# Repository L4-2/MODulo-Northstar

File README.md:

##

## Authors

- [@L42](https://www.github.com/L4-2)

## License

# Northstar

This is the MODulo mouse development board. The Kicad project files are for Kicad 9.0 and above. You are free to use this design for your own use (non-commercial) as long as you credit here in some way.

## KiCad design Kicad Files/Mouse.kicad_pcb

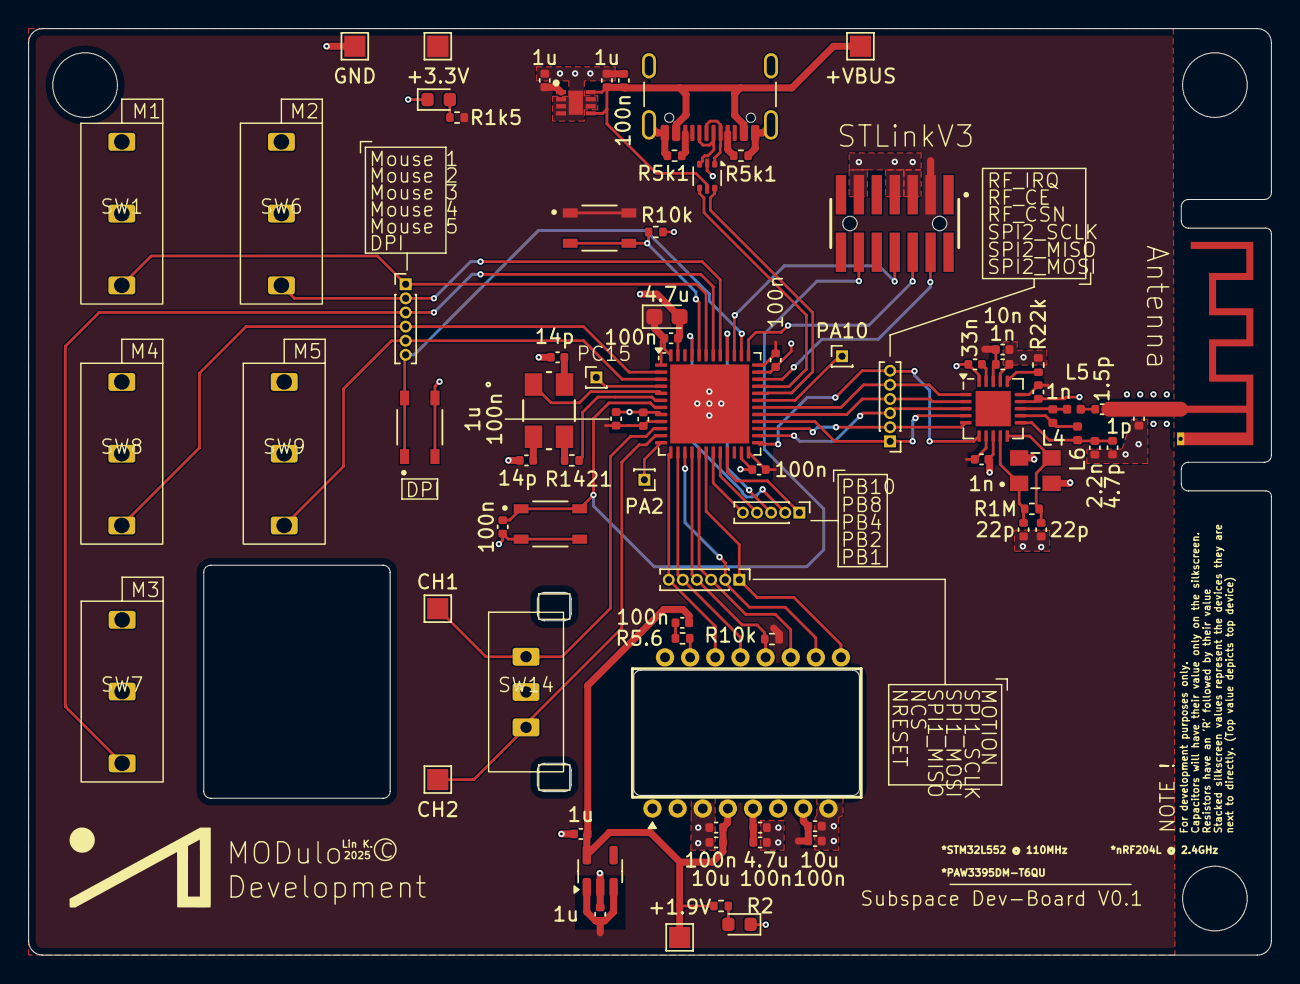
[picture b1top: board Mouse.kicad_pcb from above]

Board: 2 copper layers, 88.0 x 65.6 mm, 80 parts (0 on the bottom side), 62 nets.

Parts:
1.5p: 1.5p; C_0402_1005Metric
1n, 1n#2, 1n#3: 1n; C_0402_1005Metric
1p: 1p; C_0402_1005Metric
1u, 1u#2, 1u#3, 1u#4, 1u#5: 1u; C_0402_1005Metric
2.2n: 2.2n; C_0402_1005Metric
4.7p: 4.7p; C_0402_1005Metric
4.7u: 4.7u; C_0402_1005Metric
4.7u#2: 4.7u; CP_EIA-2012-12_Kemet-R
10n: 10n; C_0402_1005Metric
10u, 10u#2: 10u; C_0402_1005Metric
14p, 14p#2: 14p; C_0402_1005Metric
22p, 22p#2: 22p; C_0402_1005Metric
33n: 33n; C_0402_1005Metric
100n, 100n#2, 100n#3, 100n#4, 100n#5, 100n#6, 100n#7, 100n#8, 100n#9, 100n#10: 100n; C_0402_1005Metric
 +3.3V : TestPoint; TestPoint_Pad_1.5x1.5mm
+1.9V: TestPoint; TestPoint_Pad_1.5x1.5mm
+VBUS: TestPoint; TestPoint_Pad_1.5x1.5mm
AE2: Antenna; Texas_SWRA117D_2.4GHz_Left
CH1, CH2: TestPoint; TestPoint_Pad_1.5x1.5mm
D1, D2: LED; LED_0603_1608Metric
GND: TestPoint; TestPoint_Pad_1.5x1.5mm
IC1: TPS7A2133PQWDSGRQ1; SON50P200X200X80-9N
J1, J2, J9: Conn_01x06_Pin; PinHeader_1x06_P1.00mm_Vertical
J3: Conn_01x05_Pin; PinHeader_1x05_P1.00mm_Vertical
J4: USB4105-GF-A; USB_C_Receptacle_GCT_USB4105-xx-A_16P_TopMnt_Horizontal
J8: Conn_01x01_Pin; PinHeader_1x01_P1.00mm_Vertical
J12: FTSH-107-01-L-DV-K-A; SAMTEC_FTSH-107-01-L-DV-K-A
L4: 8.2n; L_0402_1005Metric
L5: 3.9n; L_0402_1005Metric
L6: 2.7n; L_0402_1005Metric
PA2, PA10: Conn_01x01_Pin; PinHeader_1x01_P1.00mm_Vertical
R1M: 1M; R_0402_1005Metric
R1k5, R2: 1k5; R_0402_1005Metric
R5.6: 5.6; R_0402_1005Metric
R5k1, R5k1#2: 5k1; R_0402_1005Metric
R10k, R10k#2: 10k; R_0402_1005Metric
R22k: 22k; R_0402_1005Metric
R1421: 1421; R_0402_1005Metric
S1, S2, S3: SKRPABE010; SW_SKRPABE010
SW1, SW6, SW7, SW8, SW9: SW_Push_SPDT; Huano
SW14: RotaryEncoder
U8: USBLC6-2P6; SOT-666
U10: nRF24L01P; QFN-20-1EP_4x4mm_P0.5mm_EP2.5x2.5mm
U11: TLV70019_SOT23-5; SOT-23-5
U12: PMW3360DM-T2QU; PMW3360
U14: STM32L552CEUxP; QFN-48-1EP_7x7mm_P0.5mm_EP5.6x5.6mm
XTAL2: ECS-80-12-30BQ-JES-TR; ECS-80-12_ECS
Y1: ECS-160-12-33Q-JES-TR; XTAL_ECS-160-12-33Q-JES-TR

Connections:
+1.9V: 1u#4.1, 10u#2.1, 100n#4.1, 100n#5.1, +1.9V.1, R2.2, U11.5 (OUT), U12.4 (VDD)
+3.3V: 1n.1, 1n#2.1, 1n#3.1, 1u#2.1, 1u#3.1, 1u#5.1, 4.7u#2.1, 10n.1, 10u.1, 100n#2.1, 100n#6.1, 100n#7.1, 100n#8.1, 100n#10.1, +3.3V.1, IC1.1 (OUT_1), J12.03, R1k5.2, R10k#2.1, S3.1, S3.2, U10.7 (VDD), U10.15 (VDD), U10.18 (VDD), U11.1 (IN), U11.3 (EN), U12.7 (VDDIO), U14.1 (VBAT), U14.9 (VDDA), U14.24 (VDD), U14.36 (VDD), U14.48 (VDD)
/BOOT: R10k.2, S3.3, S3.4, U14.44 (PH3)
/DPI: J9.6, S1.1, S1.2, U14.38 (PA15)
/Mouse1: J9.1, SW1.3 (C), U14.43 (PB7)
/Mouse2: J9.2, SW6.3 (C), U14.41 (PB5)
/Mouse3: J9.3, SW7.3 (C), U14.42 (PB6)
/Mouse4: J9.4, SW8.3 (C), U14.2 (PC13)
/Mouse5: J9.5, SW9.3 (C), U14.3 (PC14)
/NRESET: 100n#9.2, J12.12, S2.1, S2.2, U14.7 (NRST)
/RF_CE: J2.5, U10.1 (CE), U14.30 (PA9)
/RF_CSN: J2.4, U10.2 (CSN), U14.29 (PA8)
/RF_IRQ: J2.6, U10.6 (IRQ), U14.25 (PB12)
/SENSOR_MOTION: J1.1, U12.9 (MOTION), U14.18 (PB0)
/SENSOR_NCS: J1.5, U12.13 (NCS), U14.14 (PA4)
/SENSOR_NRESET: J1.6, U12.14 (NRESET), U14.13 (PA3)
/SPI1_MISO: J1.4, R10k#2.2, U12.12 (MISO), U14.16 (PA6)
/SPI1_MOSI: J1.3, U12.11 (MOSI), U14.17 (PA7)
/SPI1_SCLK: J1.2, U12.10 (SCLK), U14.15 (PA5)
/SPI2_MISO: J2.2, U10.5 (MISO), U14.27 (PB14)
/SPI2_MOSI: J2.1, U10.4 (MOSI), U14.28 (PB15)
/SPI2_SCLK: J2.3, U10.3 (SCK), U14.26 (PB13)
/SWCLK: J12.06, U14.37 (PA14)
/SWDIO: J12.04, U14.34 (PA13)
/SWO: J12.08, U14.39 (PB3)
/TIM2_CH1: CH1.1, SW14.A, U14.10 (PA0)
/TIM2_CH2: CH2.1, SW14.B, U14.11 (PA1)
/USB_DN: U8.6 (I/O1), U14.32 (PA11)
/USB_DP: U8.4 (I/O2), U14.33 (PA12)
GND: 1n.2, 1n#2.2, 1n#3.2, 1p.2, 1u.2, 1u#2.2, 1u#3.2, 1u#4.2, 1u#5.2, 2.2n.2, 4.7p.2, 4.7u.2, 4.7u#2.2, 10n.2, 10u.2, 10u#2.2, 14p.2, 14p#2.2, 22p.2, 22p#2.2, 33n.2, 100n.2, 100n#2.2, 100n#3.2, 100n#5.2, 100n#6.2, 100n#7.2, 100n#8.2, 100n#9.1, 100n#10.2, D1.1 (K), D2.1 (K), GND.1, IC1.2 (OUT_2), IC1.3 (NC_1), IC1.4 (GND), IC1.6 (NC_2), IC1.7 (IN_1), IC1.9 (EP), J4.A1 (GND), J4.A12 (GND), J4.B1 (GND), J4.B12 (GND), J4.S1 (SHIELD), J12.05, J12.07, J12.11, R5k1.1, R5k1#2.1, R10k.1, R22k.2, S1.3, S1.4, S2.3, S2.4, SW1.2 (B), SW6.2 (B), SW7.2 (B), SW8.2 (B), SW9.2 (B), SW14.C, U8.2 (GND), U10.8 (VSS), U10.14 (VSS), U10.17 (VSS), U10.20 (VSS), U11.2 (GND), U12.3 (GND), U12.8 (GNDIO), U14.8 (VSSA), U14.23 (VSS), U14.35 (VSS), U14.47 (VSS), U14.49 (VSS), Y1.2 (GND), Y1.4 (GND__1)
unnamed: 1.5p.2, 1p.1, AE2.1 (A)
unnamed: 1.5p.1, L5.2
unnamed: 100n#4.2, R5.6.2
unnamed: 14p#2.1, XTAL2.4
unnamed: 14p.1, XTAL2.2
unnamed: D1.2 (A), R1k5.1
unnamed: D2.2 (A), R2.1
unnamed: J3.1, U14.21 (PB10)
unnamed: J3.2, U14.45 (PB8)
unnamed: J3.3, U14.40 (PB4)
unnamed: J3.4, U14.20 (PB2)
unnamed: J3.5, U14.19 (PB1)
unnamed: J4.A5 (CC1), R5k1.2
unnamed: J4.B5 (CC2), R5k1#2.2
unnamed: J4.A6 (D+), J4.B6 (D+), U8.3 (I/O2)
unnamed: J4.A7 (D-), J4.B7 (D-), U8.1 (I/O1)
unnamed: J8.1, U14.4 (PC15)
unnamed: PA10.1, U14.31 (PA10)
unnamed: PA2.1, U14.12 (PA2)
unnamed: R1421.2, XTAL2.3
unnamed: L4.2, L6.1, U10.12 (ANT1)
unnamed: L4.1, L5.1, U10.13 (ANT2)
unnamed: 33n.1, U10.19 (DVDD)
unnamed: R22k.1, U10.16 (IREF)
unnamed: 2.2n.1, 4.7p.1, L6.2, U10.11 (VDD_PA)
unnamed: 22p.1, R1M.2, U10.10 (XC1), Y1.3 (OUT/IN)
unnamed: 22p#2.1, R1M.1, U10.9 (XC2), Y1.1 (IN/OUT)
unnamed: R5.6.1, U12.15 (LED_P)
unnamed: 4.7u.1, 100n#3.1, U12.5 (VDDREG)
unnamed: U14.5 (PH0), XTAL2.1
unnamed: R1421.1, U14.6 (PH1)
VBUS: 1u.1, 100n.1, +VBUS.1, IC1.5 (EN), IC1.8 (IN_2), J4.A4 (VBUS), J4.A9 (VBUS), J4.B4 (VBUS), J4.B9 (VBUS), U8.5 (VBUS)

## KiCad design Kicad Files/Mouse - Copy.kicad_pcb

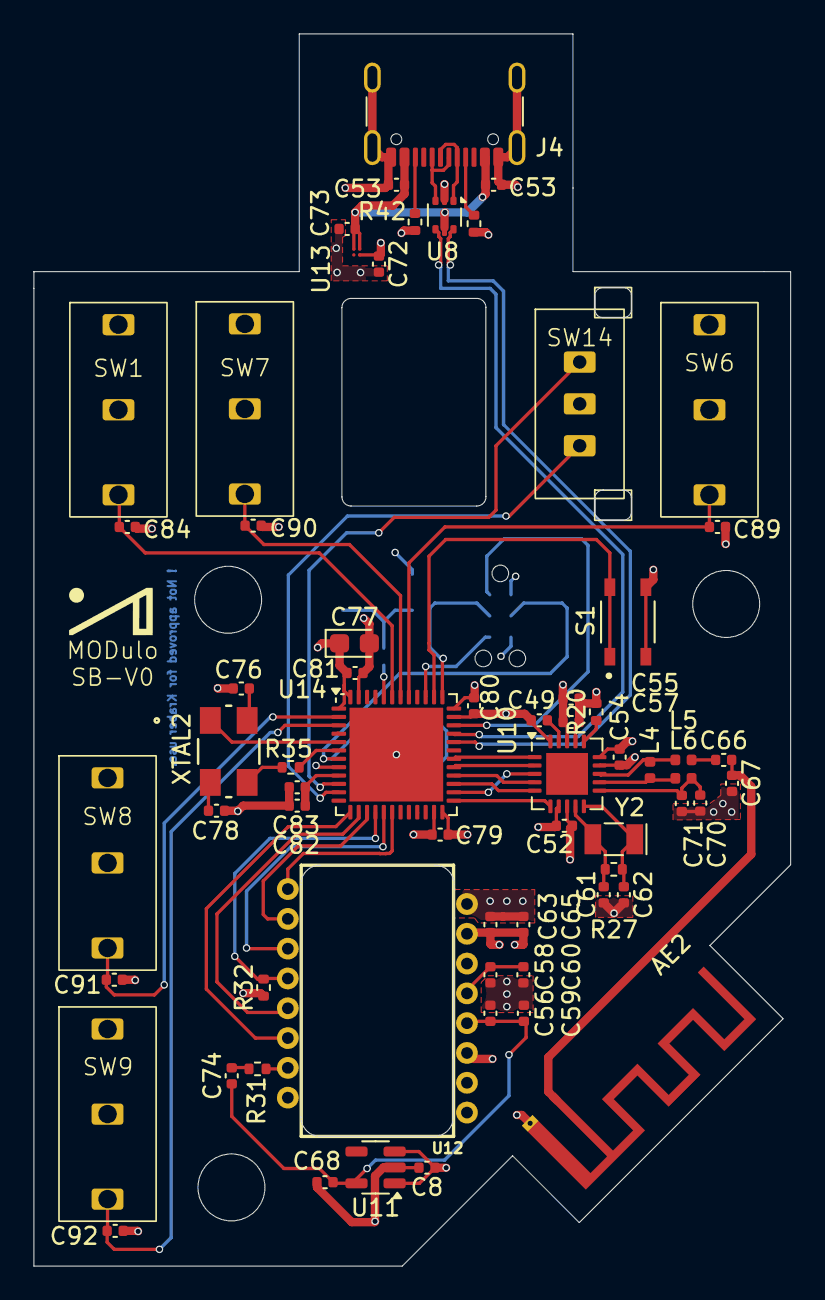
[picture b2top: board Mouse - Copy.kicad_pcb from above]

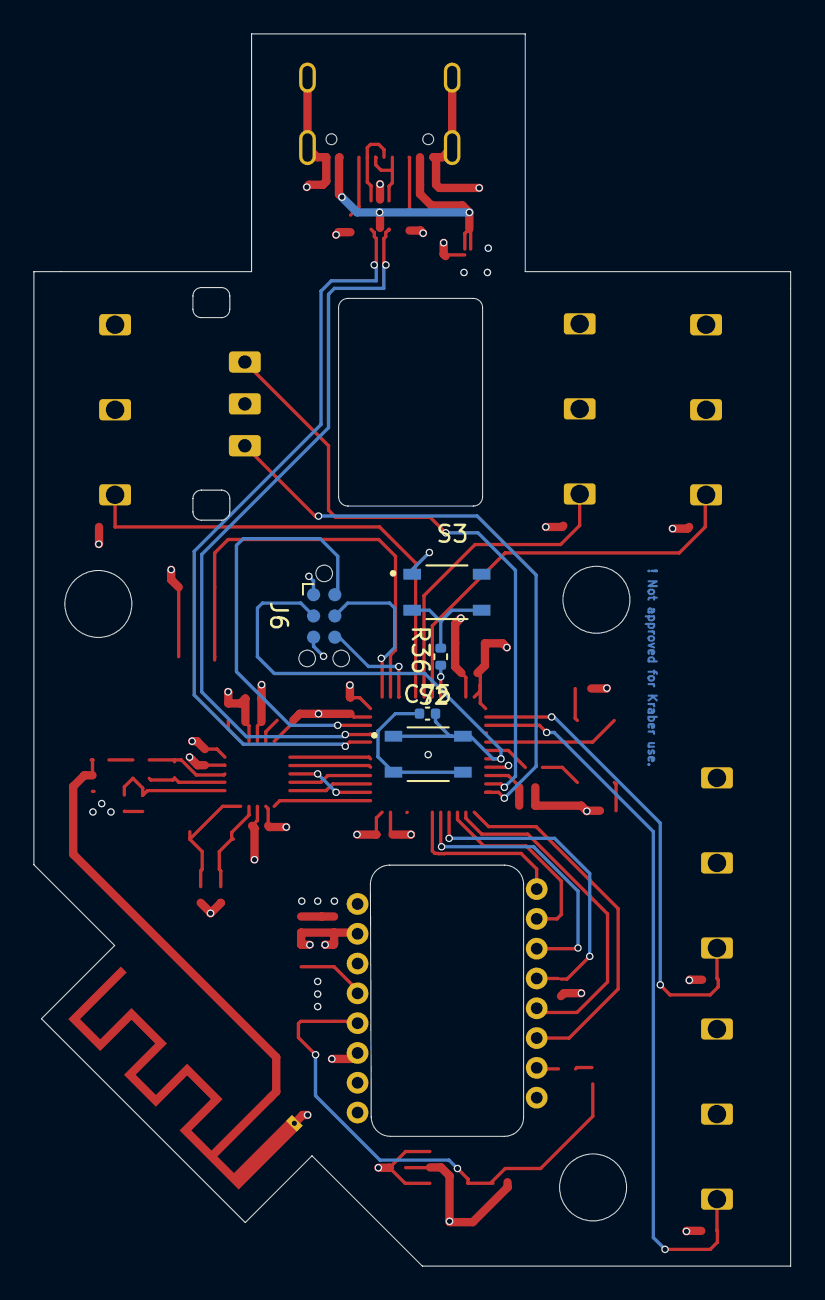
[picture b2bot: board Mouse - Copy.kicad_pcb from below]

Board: 4 copper layers, 45.2 x 73.6 mm, 69 parts (5 on the bottom side), 52 nets.

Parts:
AE2: Antenna; Texas_SWRA117D_2.4GHz_Left
C8, C68, C72, C73, C83: 1u; C_0402_1005Metric
C49: 10n; C_0402_1005Metric
C52, C54, C55: 1n; C_0402_1005Metric
C53, C53#2, C58, C60, C65, C74, C75, C79, C80, C81, C82, C84, C89, C90, C91, C92: 100n; C_0402_1005Metric
C56, C63: 10u; C_0402_1005Metric
C57: 33n; C_0402_1005Metric
C59: 4.7u; C_0402_1005Metric
C61, C62: 22p; C_0402_1005Metric
C66: 1.5p; C_0402_1005Metric
C67: 1p; C_0402_1005Metric
C70: 2.2n; C_0402_1005Metric
C71: 4.7n; C_0402_1005Metric
C76, C78: 14p; C_0402_1005Metric
C77: 4.7u; CP_EIA-2012-12_Kemet-R
J4: USB_C_Receptacle_USB2.0_14P; USB_C_Receptacle_GCT_USB4105-xx-A_16P_TopMnt_Horizontal
J6: Conn_ARM_SWD_TagConnect_TC2030; Tag-Connect_TC2030-IDC-NL_2x03_P1.27mm_Vertical
L4: 8.2n; L_0402_1005Metric
L5: 3.9n; L_0402_1005Metric
L6: 2.7n; L_0402_1005Metric
R20: 22k; R_0402_1005Metric
R27: 1M; R_0402_1005Metric
R31: 5.6; R_0402_1005Metric
R32, R36: 10k; R_0402_1005Metric
R35: 1421; R_0402_1005Metric
R41, R42: 5k1; R_0402_1005Metric
S1, S2, S3: SKRPABE010; SW_SKRPABE010
SW1, SW6, SW7, SW8, SW9: SW_Push_SPDT; Huano
SW14: RotaryEncoder
U8: USBLC6-2P6; SOT-666
U10: nRF24L01P; QFN-20-1EP_4x4mm_P0.5mm_EP2.5x2.5mm
U11: TLV70019_SOT23-5; SOT-23-5
U12: PMW3360DM-T2QU; PMW3360
U13: NCP161BFCS330T2G; WLCSP4_P6XP6_ONS
U14: STM32L552CEUxP; QFN-48-1EP_7x7mm_P0.5mm_EP5.6x5.6mm
XTAL2: ECS-80-12-30BQ-JES-TR; ECS-80-12_ECS
Y2: Crystal; Crystal_SMD_MicroCrystal_CC7V-T1A-2Pin_3.2x1.5mm

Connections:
+1.9V: C56.1, C58.1, C68.1, C74.1, U11.5 (OUT), U12.4 (VDD)
+3.3V: C8.1, C49.1, C52.1, C54.1, C55.1, C63.1, C65.1, C72.1, C77.1, C79.1, C80.1, C81.1, C82.1, C83.1, J6.1 (VCC), R32.1, S3.1, S3.2, U10.7 (VDD), U10.15 (VDD), U10.18 (VDD), U11.1 (IN), U11.3 (EN), U12.7 (VDDIO), U13.A2 (OUT), U14.1 (VBAT), U14.9 (VDDA), U14.24 (VDD), U14.36 (VDD), U14.48 (VDD)
/BOOT: R36.2, S3.3, S3.4, U14.44 (PH3)
/DPI: S1.1, S1.2, U14.38 (PA15)
/Mouse1: C84.1, SW1.3 (C), U14.43 (PB7)
/Mouse2: C89.1, SW6.3 (C), U14.41 (PB5)
/Mouse3: C90.1, SW7.3 (C), U14.42 (PB6)
/Mouse4: C91.1, SW8.3 (C), U14.2 (PC13)
/Mouse5: C92.1, SW9.3 (C), U14.3 (PC14)
/NRESET: C75.2, J6.3 (~RESET), S2.1, S2.2, U14.7 (NRST)
/RF_CE: U10.1 (CE), U14.30 (PA9)
/RF_CSN: U10.2 (CSN), U14.29 (PA8)
/RF_IRQ: U10.6 (IRQ), U14.25 (PB12)
/SENSOR_MOTION: U12.9 (MOTION), U14.18 (PB0)
/SENSOR_NCS: U12.13 (NCS), U14.14 (PA4)
/SENSOR_NRESET: U12.14 (NRESET), U14.13 (PA3)
/SPI1_MISO: R32.2, U12.12 (MISO), U14.16 (PA6)
/SPI1_MOSI: U12.11 (MOSI), U14.17 (PA7)
/SPI1_SCLK: U12.10 (SCLK), U14.15 (PA5)
/SPI2_MISO: U10.5 (MISO), U14.27 (PB14)
/SPI2_MOSI: U10.4 (MOSI), U14.28 (PB15)
/SPI2_SCLK: U10.3 (SCK), U14.26 (PB13)
/SWCLK: J6.4 (SWCLK), U14.37 (PA14)
/SWDIO: J6.2 (SWDIO), U14.34 (PA13)
/SWO: J6.6 (SWO), U14.39 (PB3)
/TIM2_CH1: SW14.A, U14.10 (PA0)
/TIM2_CH2: SW14.B, U14.11 (PA1)
/USB_DN: U8.6 (I/O1), U14.32 (PA11)
/USB_DP: U8.4 (I/O2), U14.33 (PA12)
GND: C8.2, C49.2, C52.2, C53.2, C53#2.2, C54.2, C55.2, C56.2, C57.2, C58.2, C59.2, C60.2, C61.2, C62.2, C63.2, C65.2, C67.2, C68.2, C70.2, C71.2, C72.2, C73.2, C75.1, C76.2, C77.2, C78.2, C79.2, C80.2, C81.2, C82.2, C83.2, C84.2, C89.2, C90.2, C91.2, C92.2, J4.A1 (GND), J4.A12 (GND), J4.B1 (GND), J4.B12 (GND), J4.S1 (SHIELD), J6.5 (GND), R20.2, R36.1, R41.1, R42.1, S1.3, S1.4, S2.3, S2.4, SW1.2 (B), SW6.2 (B), SW7.2 (B), SW8.2 (B), SW9.2 (B), SW14.C, U8.2 (GND), U10.8 (VSS), U10.14 (VSS), U10.17 (VSS), U10.20 (VSS), U11.2 (GND), U12.3 (GND), U12.8 (GNDIO), U13.B2 (GND), U14.8 (VSSA), U14.23 (VSS), U14.35 (VSS), U14.47 (VSS), U14.49 (VSS)
unnamed: AE2.1 (A), C66.2, C67.1
unnamed: C66.1, L5.2
unnamed: C74.2, R31.2
unnamed: C76.1, XTAL2.4
unnamed: C78.1, XTAL2.2
unnamed: J4.A5 (CC1), R42.2
unnamed: J4.B5 (CC2), R41.2
unnamed: J4.A6 (D+), J4.B6 (D+), U8.3 (I/O2)
unnamed: J4.A7 (D-), J4.B7 (D-), U8.1 (I/O1)
unnamed: R35.2, XTAL2.3
unnamed: L4.2, L6.1, U10.12 (ANT1)
unnamed: L4.1, L5.1, U10.13 (ANT2)
unnamed: C57.1, U10.19 (DVDD)
unnamed: R20.1, U10.16 (IREF)
unnamed: C70.1, C71.1, L6.2, U10.11 (VDD_PA)
unnamed: C62.1, R27.2, U10.10 (XC1), Y2.1
unnamed: C61.1, R27.1, U10.9 (XC2), Y2.2
unnamed: R31.1, U12.15 (LED_P)
unnamed: C59.1, C60.1, U12.5 (VDDREG)
unnamed: U14.5 (PH0), XTAL2.1
unnamed: R35.1, U14.6 (PH1)
VBUS: C53.1, C53#2.1, C73.1, J4.A4 (VBUS), J4.A9 (VBUS), J4.B4 (VBUS), J4.B9 (VBUS), U8.5 (VBUS), U13.A1 (IN), U13.B1 (EN)

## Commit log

2025-08-27 Update README with project details and logo
2025-08-27 7Deg
2025-08-27 Update logo image link in README
2025-08-28 Remove unnecessary header from README
2025-08-28 Fix image links in README.md
2025-09-11 Create placeholder
2025-09-11 Kicad project files
2025-09-12 3D Render Screenshot
2025-09-22 Rename Screenshot 2025-08-27 215550.png to Schematic.png

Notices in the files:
README.md:
[GNU License](https://choosealicense.com/licenses/gpl-3.0/)
